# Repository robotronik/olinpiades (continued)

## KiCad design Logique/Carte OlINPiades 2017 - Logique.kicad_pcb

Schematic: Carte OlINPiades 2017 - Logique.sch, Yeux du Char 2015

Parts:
C1, C2: 100n; C_0805_2012Metric_Pad1.15x1.40mm_HandSolder
C3, C7, C8: 100nF; C_0805_2012Metric_Pad1.15x1.40mm_HandSolder
C4: 1µF; C_0805_2012Metric_Pad1.15x1.40mm_HandSolder
C5: 47µF; C_0805_2012Metric_Pad1.15x1.40mm_HandSolder
C6, C9: C; C_1206_3216Metric_Pad1.42x1.75mm_HandSolder
D1, D2, D3, D4, D5, D6, D7, D8, D9, D10, D11, D12, D13, D14, D15, D16: BAT54CW; SOT-323_SC-70_Handsoldering
D17: RFN2L4STE25; D_SMA_Handsoldering
JP1: JUMPER3; PinHeader_1x03_P2.54mm_Vertical
JP2: JUMPER; R_1206_3216Metric_Pad1.42x1.75mm_HandSolder
P1, P2: CONN_01X32; PinHeader_1x32_P2.54mm_Vertical
P3, P6: CONN_01X02; Molex_Mini-Fit_Jr_5566-02A_2x01_P4.20mm_Vertical
P4: CONN_01X06; PinHeader_1x06_P2.54mm_Horizontal
P5: CONN_01X04; PinHeader_1x04_P2.54mm_Horizontal
P7: CONN_FREE_01X03; PinHeader_1x03_P2.54mm_Vertical
Q1, Q2, Q3, Q4, Q5, Q6, Q7, Q8: MMPQ2907A; SOIC-16_3.9x9.9mm_P1.27mm
Q9: DSS4160T; SOT-23_Handsoldering
R1, R2, R3, R4, R5, R6, R7, R8, R9, R10, R11, R12, R13, R14, R15, R16, R17, R18, R19, R20, R21, R22, R23, R24, R25, R26, R27, R28, R29, R30, R31, R32: 470; R_0603_1608Metric_Pad1.05x0.95mm_HandSolder
R33: 8.2; R_4020_10251Metric_Pad1.65x5.30mm_HandSolder
R34: 1.7k; R_0603_1608Metric_Pad1.05x0.95mm_HandSolder
R35, R36: 4k; R_0603_1608Metric_Pad1.05x0.95mm_HandSolder
R37: R; R_1206_3216Metric_Pad1.42x1.75mm_HandSolder
R38: 10kR; R_1206_3216Metric_Pad1.42x1.75mm_HandSolder
S1, S2: CAT4016; TSSOP-24_4.4x7.8mm_P0.65mm
U1: 74AHC1G; SOT-23-5_HandSoldering
U2, U3: CD74HC154; SOIC-24W_7.5x15.4mm_P1.27mm
U4: STM32F303K8; LQFP-32_7x7mm_P0.8mm
U5: NCP59301DSS33R4G; TO-263-5_TabPin3
Y1: Crystal; Crystal_HC49-4H_Vertical

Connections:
+3V3: C1.2, C2.2, C3.1, C5.1, C7.1, C8.1, JP1.3, P5.2, Q1.10, Q1.12, Q1.14, Q1.16, Q2.10, Q2.12, Q2.14, Q2.16, Q3.10, Q3.12, Q3.14, Q3.16, Q4.10, Q4.12, Q4.14, Q4.16, Q5.10, Q5.12, Q5.14, Q5.16, Q6.10, Q6.12, Q6.14, Q6.16, Q7.10, Q7.12, Q7.14, Q7.16, Q8.10, Q8.12, Q8.14, Q8.16, S1.24, S2.24, U1.5, U2.24, U3.24, U4.1 (VDD), U4.5 (VDDA), U4.17 (VDD), U5.4
+5V: C4.1, D17.1 (K), U5.1, U5.2
BLANK: S1.21, S2.21, U4.7 (PA1)
CLK_COL: S1.3, S2.3, U4.21 (PA11)
DATA: U2.18, U3.18, U4.10 (PA4)
F1: P7.1, U4.30 (PB7)
F2: P7.2, U4.29 (PB6)
F3: P7.3, U4.28 (PB5)
GND: C1.1, C2.1, C3.2, C4.2, C5.2, C6.2, C7.2, C8.2, C9.2, JP1.1, P3.1, P4.1, P5.1, Q9.2, R35.1, R36.1, S1.1, S2.1, U1.3, U2.12, U3.12, U4.16 (VSS), U4.32 (VSS), U5.3
JTDI: P4.6, U4.25 (PA15)
JTDO: P4.5, U4.26 (PB3)
LATCH_COL: S1.4, S2.4, U4.22 (PA12)
LINE_0: U2.23, U3.23, U4.15 (PB1)
LINE_1: U2.22, U3.22, U4.14 (PB0)
LINE_2: U2.21, U3.21, U4.13 (PA7)
LINE_3: U2.20, U3.20, U4.12 (PA6)
LINE_4: U1.2, U2.19, U4.11 (PA5)
NRST: JP2.1, P4.4, U4.4 (NRST)
unnamed: C6.1, R37.2, Y1.2
unnamed: C9.1, U4.2 (PF0), Y1.1
unnamed: D1.1, P1.1, Q1.1, Q1.2
unnamed: D1.2, P1.2, Q1.3, Q1.4
unnamed: D1.3, D2.3, D3.3, D4.3, D5.3, D6.3, D7.3, D8.3, D9.3, D10.3, D11.3, D12.3, D13.3, D14.3, D15.3, D16.3, R33.1
unnamed: D2.1, P1.3, Q1.5, Q1.6
unnamed: D2.2, P1.4, Q1.7, Q1.8
unnamed: D3.1, P1.5, Q2.1, Q2.2
unnamed: D3.2, P1.6, Q2.3, Q2.4
unnamed: D4.1, P1.7, Q2.5, Q2.6
unnamed: D4.2, P1.8, Q2.7, Q2.8
unnamed: D5.1, P1.9, Q3.1, Q3.2
unnamed: D5.2, P1.10, Q3.3, Q3.4
unnamed: D6.1, P1.11, Q3.5, Q3.6
unnamed: D6.2, P1.12, Q3.7, Q3.8
unnamed: D7.1, P1.13, Q4.1, Q4.2
unnamed: D7.2, P1.14, Q4.3, Q4.4
unnamed: D8.1, P1.15, Q4.5, Q4.6
unnamed: D8.2, P1.16, Q4.7, Q4.8
unnamed: D9.1, P1.17, Q5.1, Q5.2
unnamed: D9.2, P1.18, Q5.3, Q5.4
unnamed: D10.1, P1.19, Q5.5, Q5.6
unnamed: D10.2, P1.20, Q5.7, Q5.8
unnamed: D11.1, P1.21, Q6.1, Q6.2
unnamed: D11.2, P1.22, Q6.3, Q6.4
unnamed: D12.1, P1.23, Q6.5, Q6.6
unnamed: D12.2, P1.24, Q6.7, Q6.8
unnamed: D13.1, P1.25, Q7.1, Q7.2
unnamed: D13.2, P1.26, Q7.3, Q7.4
unnamed: D14.1, P1.27, Q7.5, Q7.6
unnamed: D14.2, P1.28, Q7.7, Q7.8
unnamed: D15.1, P1.29, Q8.1, Q8.2
unnamed: D15.2, P1.30, Q8.3, Q8.4
unnamed: D16.1, P1.31, Q8.5, Q8.6
unnamed: D16.2, P1.32, Q8.7, Q8.8
unnamed: D17.2 (A), P3.2
unnamed: JP1.2, R38.1
unnamed: JP2.2, U4.27 (PB4)
unnamed: P2.1, S1.5
unnamed: P2.2, S1.6
unnamed: P2.3, S1.7
unnamed: P2.4, S1.8
unnamed: P2.5, S1.9
unnamed: P2.6, S1.10
unnamed: P2.7, S1.11
unnamed: P2.8, S1.12
unnamed: P2.9, S1.13
unnamed: P2.10, S1.14
unnamed: P2.11, S1.15
unnamed: P2.12, S1.16
unnamed: P2.13, S1.17
unnamed: P2.14, S1.18
unnamed: P2.15, S1.19
unnamed: P2.16, S1.20
unnamed: P2.17, S2.5
unnamed: P2.18, S2.6
unnamed: P2.19, S2.7
unnamed: P2.20, S2.8
unnamed: P2.21, S2.9
unnamed: P2.22, S2.10
unnamed: P2.23, S2.11
unnamed: P2.24, S2.12
unnamed: P2.25, S2.13
unnamed: P2.26, S2.14
unnamed: P2.27, S2.15
unnamed: P2.28, S2.16
unnamed: P2.29, S2.17
unnamed: P2.30, S2.18
unnamed: P2.31, S2.19
unnamed: P2.32, S2.20
unnamed: Q1.9, R4.2
unnamed: Q1.11, R3.2
unnamed: Q1.13, R2.2
unnamed: Q1.15, R1.2
unnamed: Q2.9, R8.2
unnamed: Q2.11, R7.2
unnamed: Q2.13, R6.2
unnamed: Q2.15, R5.2
unnamed: Q3.9, R12.2
unnamed: Q3.11, R11.2
unnamed: Q3.13, R10.2
unnamed: Q3.15, R9.2
unnamed: Q4.9, R16.2
unnamed: Q4.11, R15.2
unnamed: Q4.13, R14.2
unnamed: Q4.15, R13.2
unnamed: Q5.9, R20.2
unnamed: Q5.11, R19.2
unnamed: Q5.13, R18.2
unnamed: Q5.15, R17.2
unnamed: Q6.9, R24.2
unnamed: Q6.11, R23.2
unnamed: Q6.13, R22.2
unnamed: Q6.15, R21.2
unnamed: Q7.9, R28.2
unnamed: Q7.11, R27.2
unnamed: Q7.13, R26.2
unnamed: Q7.15, R25.2
unnamed: Q8.9, R32.2
unnamed: Q8.11, R31.2
unnamed: Q8.13, R30.2
unnamed: Q8.15, R29.2
unnamed: Q9.1, R34.1
unnamed: Q9.3, R33.2
unnamed: R1.1, U2.1
unnamed: R2.1, U2.2
unnamed: R3.1, U2.3
unnamed: R4.1, U2.4
unnamed: R5.1, U2.5
unnamed: R6.1, U2.6
unnamed: R7.1, U2.7
unnamed: R8.1, U2.8
unnamed: R9.1, U2.9
unnamed: R10.1, U2.10
unnamed: R11.1, U2.11
unnamed: R12.1, U2.13
unnamed: R13.1, U2.14
unnamed: R14.1, U2.15
unnamed: R15.1, U2.16
unnamed: R16.1, U2.17
unnamed: R17.1, U3.1
unnamed: R18.1, U3.2
unnamed: R19.1, U3.3
unnamed: R20.1, U3.4
unnamed: R21.1, U3.5
unnamed: R22.1, U3.6
unnamed: R23.1, U3.7
unnamed: R24.1, U3.8
unnamed: R25.1, U3.9
unnamed: R26.1, U3.10
unnamed: R27.1, U3.11
unnamed: R28.1, U3.13
unnamed: R29.1, U3.14
unnamed: R30.1, U3.15
unnamed: R31.1, U3.16
unnamed: R32.1, U3.17
unnamed: R35.2, S1.23
unnamed: R36.2, S2.23
unnamed: R37.1, U4.3 (PF1)
unnamed: R38.2, U4.31 (BOOT0)
unnamed: S1.22, S2.2
unnamed: U1.4, U3.19
PURGE: R34.2, U4.6 (PA0)
RX_EYE: P6.1, U4.9 (PA3)
RX_SERIAL: P5.3, U4.20 (PA10)
SERIAL_IN: S1.2, U4.18 (PA8)
SWCLK: P4.2, U4.24 (PA14)
SWDIO: P4.3, U4.23 (PA13)
TX_EYE: P6.2, U4.8 (PA2)
TX_SERIAL: P5.4, U4.19 (PA9)

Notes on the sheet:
SW/JTAG
UART_DEBUG
UART_M/S
ALIM 5V BUCK
Attention, vérifier la footprint par rapport au composant réel !! (R33)

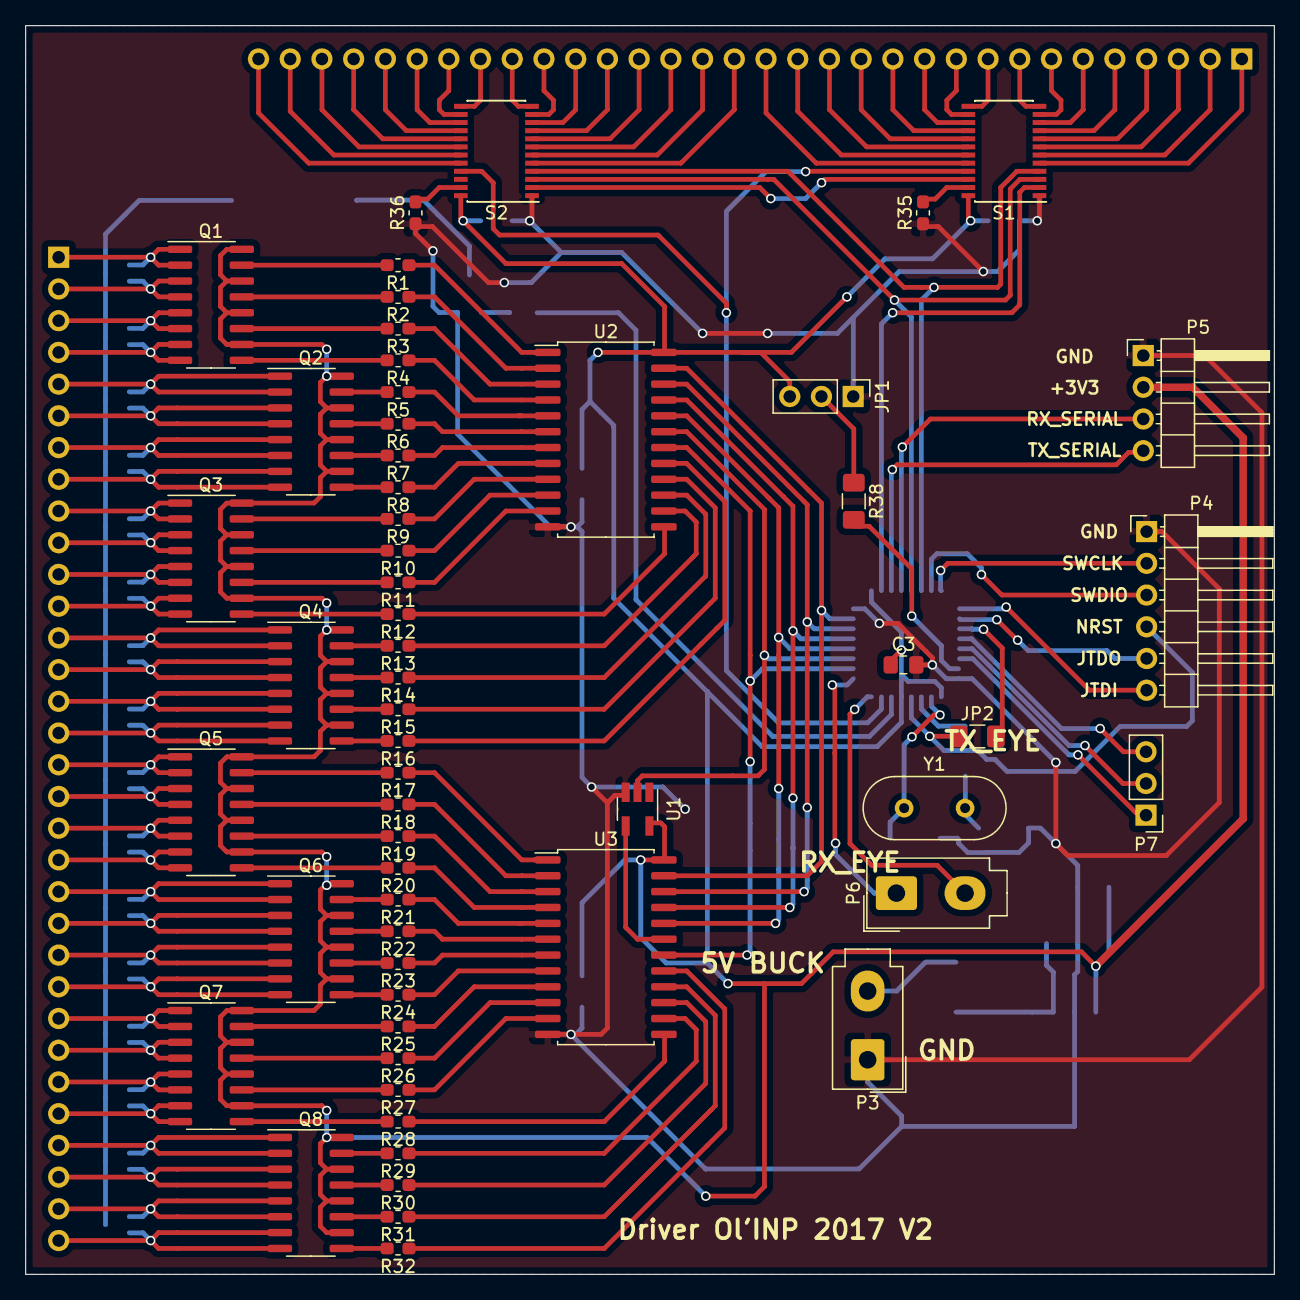
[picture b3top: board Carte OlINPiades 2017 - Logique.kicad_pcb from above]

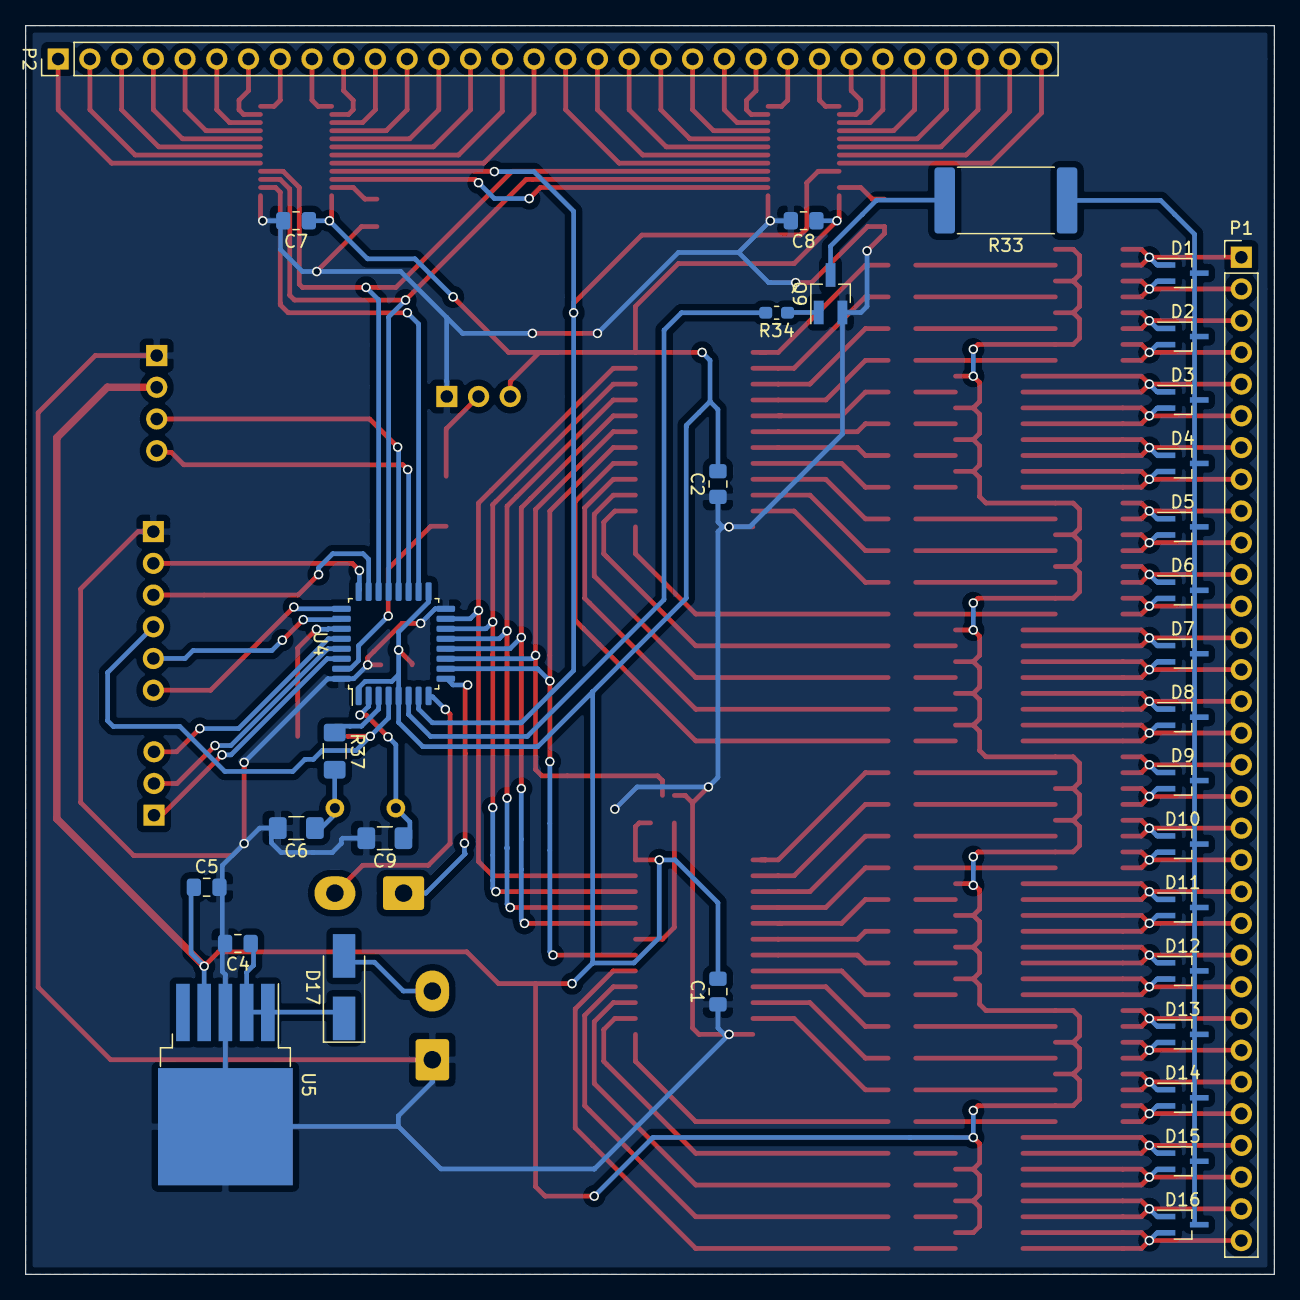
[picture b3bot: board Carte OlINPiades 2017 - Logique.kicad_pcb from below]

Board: 2 copper layers, 100.0 x 100.0 mm, 90 parts (33 on the bottom side), 168 nets.

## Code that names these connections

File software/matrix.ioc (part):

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Mcu.Name=STM32F303K(6-8)Tx
Mcu.Package=LQFP32
Mcu.UserName=STM32F303K8Tx
PA0.GPIOParameters=GPIO_Speed,GPIO_Label
PA0.GPIO_Label=PURGE
PA0.GPIO_Speed=GPIO_SPEED_FREQ_HIGH
PA0.Signal=GPIO_Output
PA1.GPIOParameters=GPIO_Speed,GPIO_Label
PA1.GPIO_Label=BLANK
PA1.GPIO_Speed=GPIO_SPEED_FREQ_HIGH
PA1.Signal=GPIO_Output
PA10.GPIOParameters=GPIO_Speed,GPIO_Label
PA10.GPIO_Label=SERIAL_IN
PA10.GPIO_Speed=GPIO_SPEED_FREQ_HIGH
PA10.Signal=GPIO_Output
PA11.GPIOParameters=GPIO_Speed,GPIO_Label
PA11.GPIO_Label=CLK_COL
PA11.GPIO_Speed=GPIO_SPEED_FREQ_HIGH
PA11.Signal=GPIO_Output
PA12.GPIOParameters=GPIO_Speed,GPIO_Label
PA12.GPIO_Label=LATCH_COL
PA12.GPIO_Speed=GPIO_SPEED_FREQ_HIGH
PA12.Signal=GPIO_Output
PA13.Mode=Serial_Wire
PA13.Signal=SYS_JTMS-SWDIO
PA14.Mode=Serial_Wire
PA14.Signal=SYS_JTCK-SWCLK
PA2.Mode=Asynchronous
PA2.Signal=USART2_TX
PA3.Mode=Asynchronous
PA3.Signal=USART2_RX
PA4.GPIOParameters=GPIO_Speed,GPIO_Label
PA4.GPIO_Label=DATA
PA4.GPIO_Speed=GPIO_SPEED_FREQ_HIGH
PA4.Signal=GPIO_Output
PA5.GPIOParameters=GPIO_Speed,GPIO_Label
PA5.GPIO_Label=LINE_4
PA5.GPIO_Speed=GPIO_SPEED_FREQ_HIGH
PA5.Signal=GPIO_Output
PA6.GPIOParameters=GPIO_Speed,GPIO_Label
PA6.GPIO_Label=LINE_3
PA6.GPIO_Speed=GPIO_SPEED_FREQ_HIGH
PA6.Signal=GPIO_Output
PA7.GPIOParameters=GPIO_Speed,GPIO_Label
PA7.GPIO_Label=LINE_2
PA7.GPIO_Speed=GPIO_SPEED_FREQ_HIGH
PA7.Signal=GPIO_Output
PB0.GPIOParameters=GPIO_Speed,GPIO_Label
PB0.GPIO_Label=LINE_1
PB0.GPIO_Speed=GPIO_SPEED_FREQ_HIGH
PB0.Signal=GPIO_Output
PB1.GPIOParameters=GPIO_Speed,GPIO_Label
PB1.GPIO_Label=LINE_0
PB1.GPIO_Speed=GPIO_SPEED_FREQ_HIGH
PB1.Signal=GPIO_Output
RCC.HSEPLLFreq_Value=8000000
RCC.HSE_VALUE=8000000
RCC.SYSCLKFreq_VALUE=64000000
RCC.SYSCLKSourceVirtual=RCC_SYSCLKSOURCE_PLLCLK
board=matrix

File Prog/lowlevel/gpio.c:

/**
  ******************************************************************************
  * File Name          : gpio.c
  * Description        : This file provides code for the configuration
  *                      of all used GPIO pins.
  ******************************************************************************
  ** This notice applies to any and all portions of this file
  * that are not between comment pairs USER CODE BEGIN and
  * USER CODE END. Other portions of this file, whether 
  * inserted by the user or by software development tools
  * are owned by their respective copyright owners.
  *
  * COPYRIGHT(c) 2018 STMicroelectronics
  *
  * Redistribution and use in source and binary forms, with or without modification,
  * are permitted provided that the following conditions are met:
  *   1. Redistributions of source code must retain the above copyright notice,
  *      this list of conditions and the following disclaimer.
  *   2. Redistributions in binary form must reproduce the above copyright notice,
  *      this list of conditions and the following disclaimer in the documentation
  *      and/or other materials provided with the distribution.
  *   3. Neither the name of STMicroelectronics nor the names of its contributors
  *      may be used to endorse or promote products derived from this software
  *      without specific prior written permission.
  *
  * THIS SOFTWARE IS PROVIDED BY THE COPYRIGHT HOLDERS AND CONTRIBUTORS "AS IS"
  * AND ANY EXPRESS OR IMPLIED WARRANTIES, INCLUDING, BUT NOT LIMITED TO, THE
  * IMPLIED WARRANTIES OF MERCHANTABILITY AND FITNESS FOR A PARTICULAR PURPOSE ARE
  * DISCLAIMED. IN NO EVENT SHALL THE COPYRIGHT HOLDER OR CONTRIBUTORS BE LIABLE
  * FOR ANY DIRECT, INDIRECT, INCIDENTAL, SPECIAL, EXEMPLARY, OR CONSEQUENTIAL
  * DAMAGES (INCLUDING, BUT NOT LIMITED TO, PROCUREMENT OF SUBSTITUTE GOODS OR
  * SERVICES; LOSS OF USE, DATA, OR PROFITS; OR BUSINESS INTERRUPTION) HOWEVER
  * CAUSED AND ON ANY THEORY OF LIABILITY, WHETHER IN CONTRACT, STRICT LIABILITY,
  * OR TORT (INCLUDING NEGLIGENCE OR OTHERWISE) ARISING IN ANY WAY OUT OF THE USE
  * OF THIS SOFTWARE, EVEN IF ADVISED OF THE POSSIBILITY OF SUCH DAMAGE.
  *
  ******************************************************************************
  */

/* Includes ------------------------------------------------------------------*/
#include "gpio.h"
/* USER CODE BEGIN 0 */

/* USER CODE END 0 */

/*----------------------------------------------------------------------------*/
/* Configure GPIO                                                             */
/*----------------------------------------------------------------------------*/
/* USER CODE BEGIN 1 */

/* USER CODE END 1 */

/** Configure pins as 
        * Analog 
        * Input 
        * Output
        * EVENT_OUT
        * EXTI
        * Free pins are configured automatically as Analog (this feature is enabled through 
        * the Code Generation settings)
*/
void MX_GPIO_Init(void)
{

  GPIO_InitTypeDef GPIO_InitStruct;

  /* GPIO Ports Clock Enable */
  __HAL_RCC_GPIOF_CLK_ENABLE();
  __HAL_RCC_GPIOA_CLK_ENABLE();
  __HAL_RCC_GPIOB_CLK_ENABLE();

  /*Configure GPIO pin Output Level */
  HAL_GPIO_WritePin(GPIOA, PURGE_Pin|BLANK_Pin|DATA_Pin|LINE_4_Pin 
                          |LINE_3_Pin|LINE_2_Pin|SERIAL_IN_Pin|CLK_COL_Pin 
                          |LATCH_COL_Pin, GPIO_PIN_RESET);

  /*Configure GPIO pin Output Level */
  HAL_GPIO_WritePin(GPIOB, LINE_1_Pin|LINE_0_Pin, GPIO_PIN_RESET);

  /*Configure GPIO pins : PF0 PF1 */
  GPIO_InitStruct.Pin = GPIO_PIN_0|GPIO_PIN_1;
  GPIO_InitStruct.Mode = GPIO_MODE_ANALOG;
  GPIO_InitStruct.Pull = GPIO_NOPULL;
  HAL_GPIO_Init(GPIOF, &GPIO_InitStruct);

  /*Configure GPIO pins : PAPin PAPin PAPin PAPin 
                           PAPin PAPin PAPin PAPin 
                           PAPin */
  GPIO_InitStruct.Pin = PURGE_Pin|BLANK_Pin|DATA_Pin|LINE_4_Pin 
                          |LINE_3_Pin|LINE_2_Pin|SERIAL_IN_Pin|CLK_COL_Pin 
                          |LATCH_COL_Pin;
  GPIO_InitStruct.Mode = GPIO_MODE_OUTPUT_PP;
  GPIO_InitStruct.Pull = GPIO_NOPULL;
  GPIO_InitStruct.Speed = GPIO_SPEED_FREQ_HIGH;
  HAL_GPIO_Init(GPIOA, &GPIO_InitStruct);

  /*Configure GPIO pins : PBPin PBPin */
  GPIO_InitStruct.Pin = LINE_1_Pin|LINE_0_Pin;
  GPIO_InitStruct.Mode = GPIO_MODE_OUTPUT_PP;
  GPIO_InitStruct.Pull = GPIO_NOPULL;
  GPIO_InitStruct.Speed = GPIO_SPEED_FREQ_HIGH;
  HAL_GPIO_Init(GPIOB, &GPIO_InitStruct);

  /*Configure GPIO pin : PA15 */
  GPIO_InitStruct.Pin = GPIO_PIN_15;
  GPIO_InitStruct.Mode = GPIO_MODE_ANALOG;
  GPIO_InitStruct.Pull = GPIO_NOPULL;
  HAL_GPIO_Init(GPIOA, &GPIO_InitStruct);

  /*Configure GPIO pins : PB3 PB4 PB5 PB6 
                           PB7 */
  GPIO_InitStruct.Pin = GPIO_PIN_3|GPIO_PIN_4|GPIO_PIN_5|GPIO_PIN_6 
                          |GPIO_PIN_7;
  GPIO_InitStruct.Mode = GPIO_MODE_ANALOG;
  GPIO_InitStruct.Pull = GPIO_NOPULL;
  HAL_GPIO_Init(GPIOB, &GPIO_InitStruct);

}

/* USER CODE BEGIN 2 */

/* USER CODE END 2 */

/**
  * @}
  */

/**
  * @}
  */

/************************ (C) COPYRIGHT STMicroelectronics *****END OF FILE****/

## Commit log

2015-10-01 structure minimale de projet
2015-10-01 ajout fichiers utiles (?)
2015-10-01 ajoute un exemple sur PC
2015-10-01 ajout fichiers
2015-10-01 ajout rotation matrice, presque fonctionnel
2015-10-01 ajout fonction get_frame_line()
2015-10-01 rotation fonctionnelle
2015-10-01 nettoyage
2015-10-01 enleve des blancs et corrige un oubli
2015-10-01 calcul de la frame à afficher fait séparément + display du texte comme il faut
2015-10-02 ajoute un fichier de font
2015-10-02 gestion de l'affichage de texte presque fonctionnel mais sale
2015-10-02 déplace les fonction, nettoyage à faire
2015-10-02 structure plus propre
2015-10-02 correction bug d'affichage
2015-10-02 renomme shift_frame et shift_columns
2015-10-02 retourne l'affichage
2015-10-02 enleve fonction désuette
2015-10-02 change le texte et corrige quelques oublis
2015-10-02 la génération du texte est faite à mesure
2015-10-02 utilise la vraie largeur de caractere
2015-10-03 adding (empty) framebuffer files
2015-10-03 draw 16*h sprites in xy
2015-10-03 remove bugs, variable sprite size
2015-10-03 working on some keyframe anim
2015-10-03 anim routines finished, need to test them now
2015-10-03 animation routines works perfectly
2015-10-03 some fancy tests :]
2015-10-03 cleaning
2015-10-03 changing sprite
2015-10-03 adding framebuffer, sprites, key animation
2015-10-04 a cute animated eye on extasy added. Animation needs to be tweaked a bit more. If someone could redraw the sprites for the eye so it would look like more agreesive, that'd be great :]
2015-10-04 upset expression loks a bit more ... upset
2015-10-04 ongoing devil eyes sketches
2015-10-04 ongoing devil eyes sketches : separating eye and pupil
2015-10-04 pixels modified
2015-10-05 l'oeil diabolique est fini! Animations encore à fignoler. Ajout d'une fonction de dessin de sprites avec clipping ( afin de ne dessiner la pupille que dans l'oeil et pas en dehors).
2015-10-07 ajout du séquenceur de démos, du rendu de caractères, et commencement d'un scrolling text pouvant être chaîné avec un autre afficheur
2015-10-08 ajoute les routines hardware
2015-10-08 working on scrollingtext
2015-10-08 correction bug hard
2015-10-08 Testing a flash animation
2015-10-08 ajoute la fonction write_column()
2015-10-08 viré exe du repo
2015-10-09 fix broken things
2015-10-09 left/right is finished, config in Makefile
2015-10-09 clean exe
2015-10-09 moche
2015-10-09 mieux mais moche
2015-10-09 final release (ou pas)
2015-10-22 adaptation du makefile aux nouveaux makefiles autour
2015-10-22 la simulation sur PC fonctionne ;)
2015-10-23 retournement des yeux pour PC
2016-04-17 clean repo and build process
2019-10-03 Remove everything
2019-10-03 New structure, pcbs
2019-10-03 final matrix
2019-10-03 new makefile
2019-10-03 modif empreinte STM32
2019-10-03 modif marquage
2019-10-03 ajout 3.3V pour esp
2019-10-03 gerber
2019-10-03 Remove old files
2019-10-03 reorganize code a bit
2019-10-03 Refactoring tree of git
2019-10-03 fix build, remove warnings
2019-10-03 fix gitignore, add warnings
2019-10-04 Fix makefile tests
2019-10-04 get code from cdfr2018
2019-10-04 add function
2019-10-04 should not work
2019-10-04 should work, sorry
2019-10-04 Add new project, libopencm3 and clean code
2019-10-04 Kicad 5, argh !
2019-10-04 Continue
2019-10-04 begin frames generation and storage
2019-10-05 Integrate frames_generator into main proj
2019-10-05 fix build
2019-10-05 remove includes from header
2019-10-05 Add tests native, fix sync
2019-10-05 Add error when not cross build
2019-10-05 Fix types, add weak for native tests.
2019-10-05 frame generation ok
2019-10-05 small precision
2019-10-06 Update schematics and PCB to kicad5
2019-10-06 Port matrice to kicad 5
2019-10-06 Remove librariers
2019-10-07 move install_udev, chmod +x
2019-10-08 Fix mirror, set debug by default, error on no libopencm3
2019-10-08 PUTAIN DE GPIO SA MÈRE T'AURAIS PU CHANGER LE CODE CONNARD
2019-10-08 Add old frames generator code. The format should be converted from uint8[][] to uint32[].
2019-10-08 Remove old code
2019-10-10 ajout animation
2019-10-10 ajout dans images
2019-10-10 premiere version des yeux
2023-06-18 mise a jour important, nouvelle carte et programme, cumul des animations des derniers annee
2023-06-18 changement de commit pour la librairie libopencm3
2023-06-18 changement de commit pour libopencm3 again...
2023-06-18 ajout des readme
2024-11-07 Update Makefile
